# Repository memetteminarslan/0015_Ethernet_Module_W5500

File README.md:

# 0015_Ethernet_Module_W5500
You are seeing a large number of widely used Ethernet modules in electronic development kits. More information coming soon...

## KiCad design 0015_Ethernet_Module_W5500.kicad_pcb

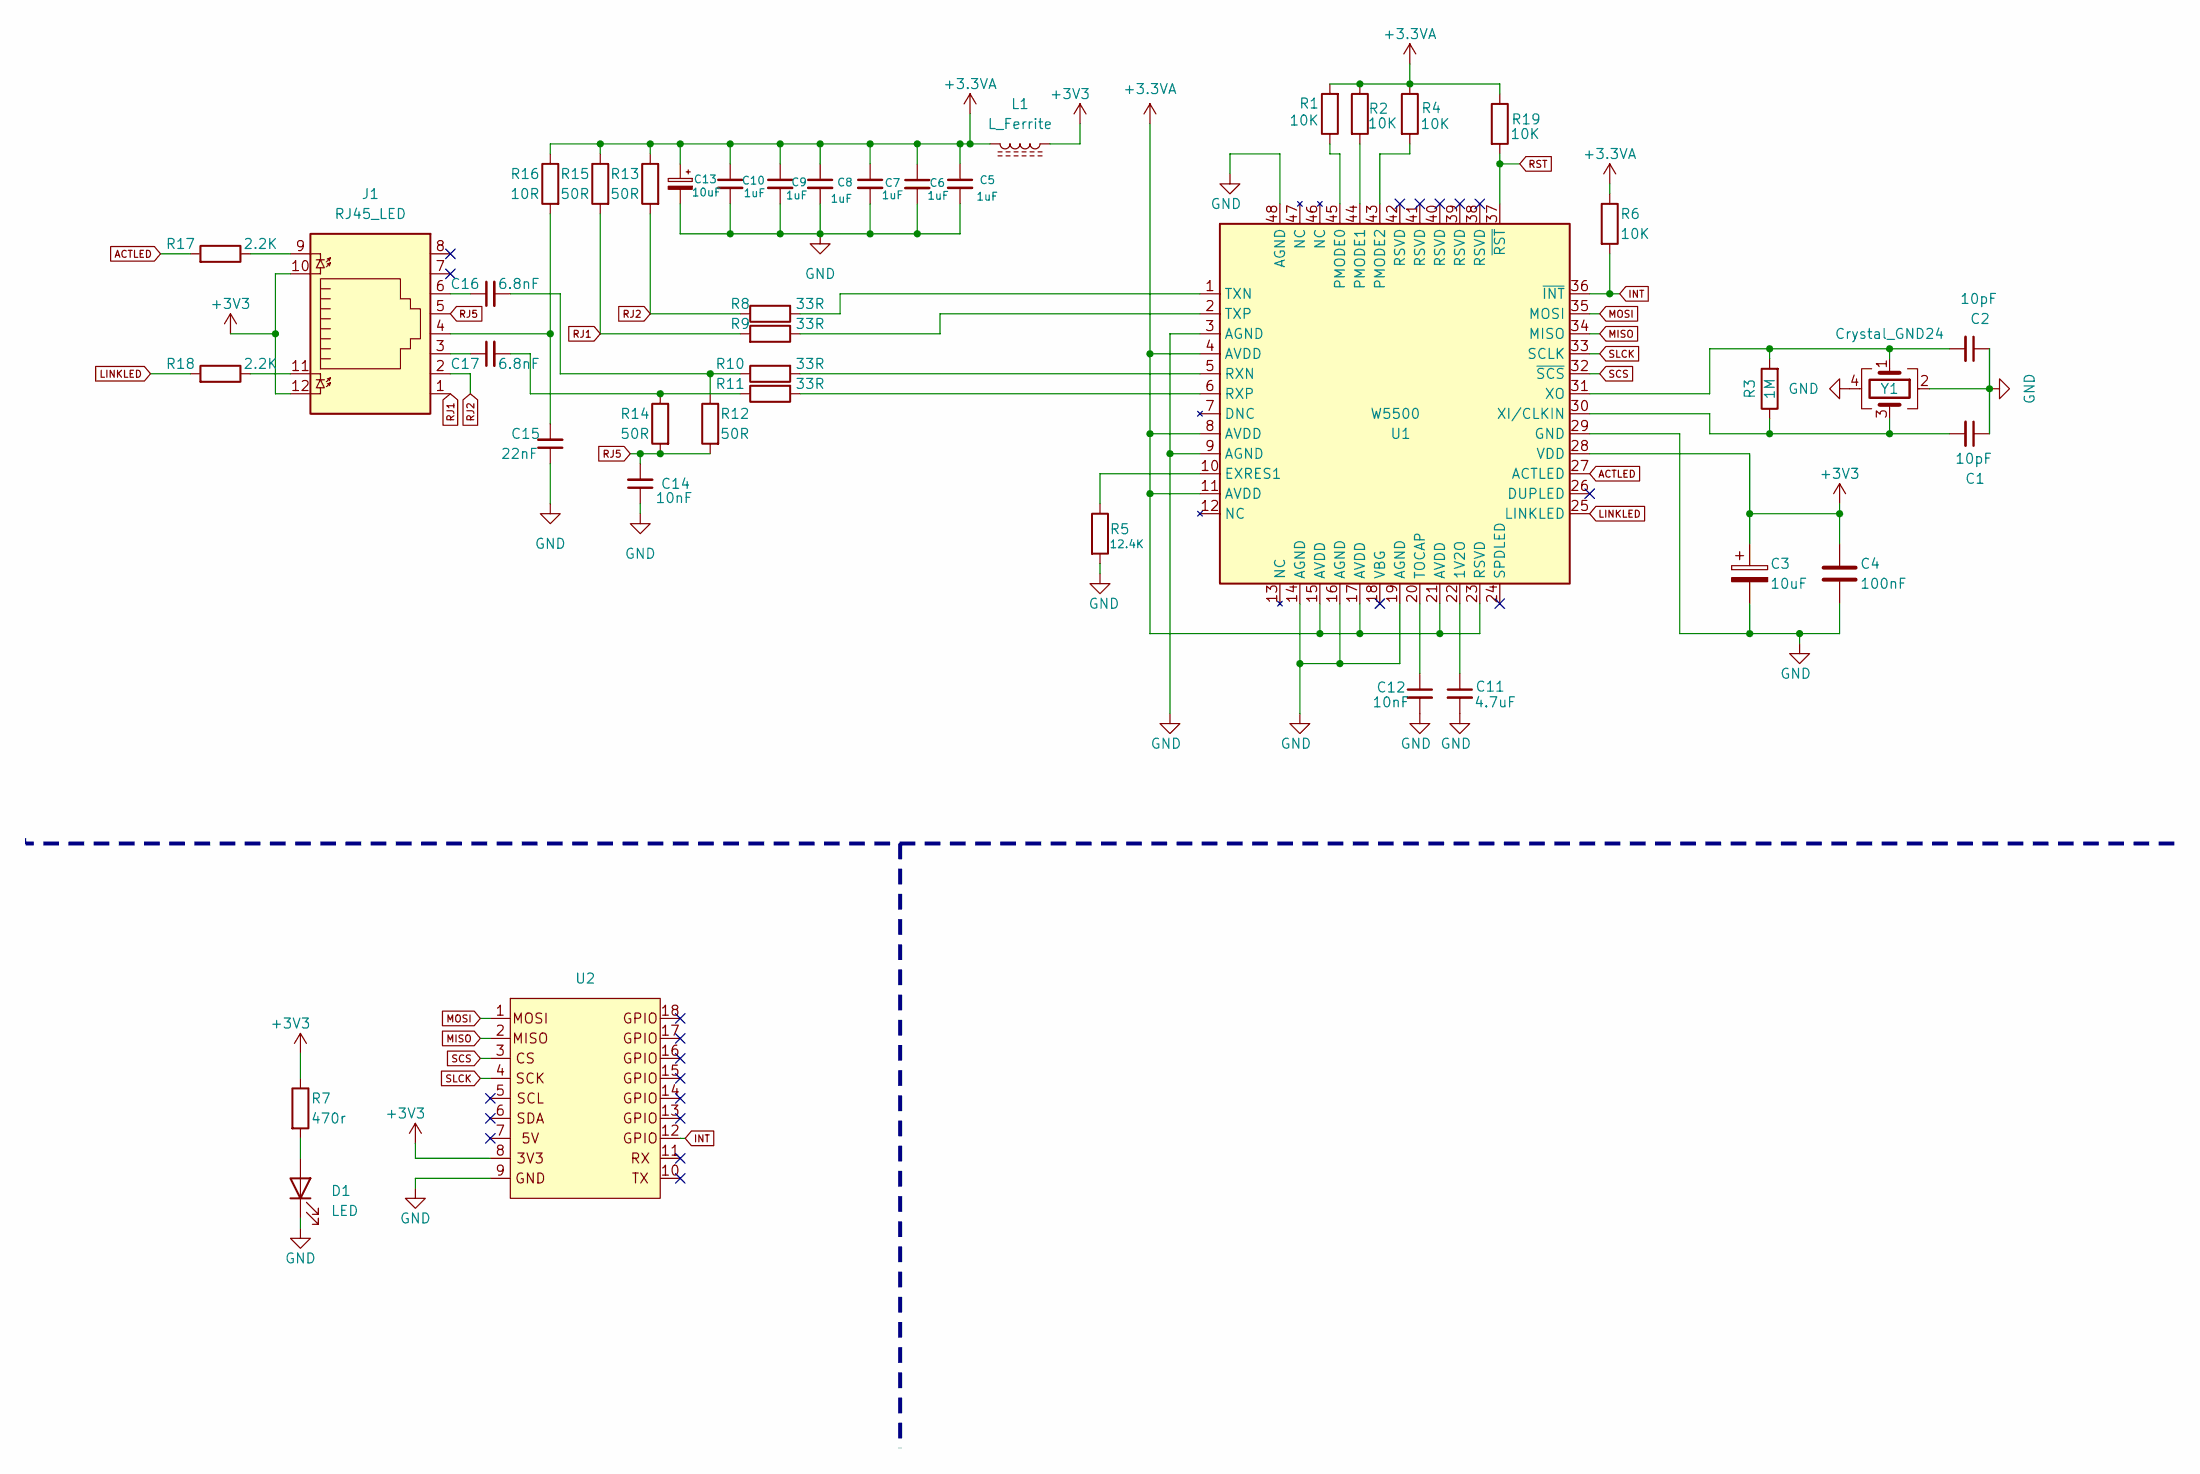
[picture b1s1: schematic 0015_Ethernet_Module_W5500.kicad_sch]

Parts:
C1, C2: 10pF; C_0805_2012Metric
C3, C13: 10uF; CP_EIA-3216-10_Kemet-I
C4: 100nF; C_0805_2012Metric
C5, C6, C7, C8, C9, C10: 1uF; C_0805_2012Metric
C11: 4.7uF; C_0805_2012Metric
C12, C14: 10nF; C_0805_2012Metric
C15: 22nF; C_0805_2012Metric
C16, C17: 6.8nF; C_0805_2012Metric
D1: LED; LED_0805_2012Metric
J1: RJ45_LED; RJ45_Hanrun_HR911105A
L1: L_Ferrite; C_0603_1608Metric
R1, R2, R4, R6, R19: 10K; R_0805_2012Metric
R3: 1M; R_0805_2012Metric
R5: 12.4K; R_0805_2012Metric
R7: 470r; R_0805_2012Metric
R8, R9, R10, R11: 33R; R_0805_2012Metric
R12, R13, R14, R15: 50R; R_0805_2012Metric
R16: 10R; R_0805_2012Metric
R17, R18: 2.2K; R_0805_2012Metric
U1: W5500; LQFP-48_7x7mm_P0.5mm
U2: pin_header_5-3
Y1: Crystal_GND24; Crystal_SMD_EuroQuartz_MT-4Pin_3.2x2.5mm

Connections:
+3.3VA: C5.1, C6.1, C7.1, C8.1, C9.1, C10.1, C13.1, L1.1, R1.2, R2.1, R4.1, R6.1, R13.1, R15.1, R16.1, R19.1, U1.4 (AVDD), U1.8 (AVDD), U1.11 (AVDD), U1.15 (AVDD), U1.17 (AVDD), U1.21 (AVDD), U1.23 (RSVD)
+3V3: C3.1, C4.1, J1.10, J1.12, L1.2, R7.1, U1.28 (VDD), U2.8
ACTLED: R17.2, U1.27 (ACTLED)
GND: C1.1, C2.1, C3.2, C4.2, C5.2, C6.2, C7.2, C8.2, C9.2, C10.2, C11.2, C12.2, C13.2, C14.1, C15.1, D1.1 (K), R5.2, U1.3 (AGND), U1.9 (AGND), U1.14 (AGND), U1.16 (AGND), U1.19 (AGND), U1.29 (GND), U1.48 (AGND), U2.9, Y1.2, Y1.4
INT: R6.2, U1.36 (~INT), U2.12
LINKLED: R18.2, U1.25 (LINKLED)
MISO: U1.34 (MISO), U2.2
MOSI: U1.35 (MOSI), U2.1
unnamed: C15.2, J1.4, R16.2
unnamed: C16.1, J1.6
unnamed: C16.2, R10.1, R12.1
unnamed: C17.1, J1.3
unnamed: C17.2, R11.1, R14.1
unnamed: D1.2 (A), R7.2
unnamed: J1.9, R17.1
unnamed: J1.11, R18.1
unnamed: C11.1, U1.22 (1V2O)
unnamed: R5.1, U1.10 (EXRES1)
unnamed: R1.1, U1.45 (PMODE0)
unnamed: R2.2, U1.44 (PMODE1)
unnamed: R4.2, U1.43 (PMODE2)
unnamed: R10.2, U1.5 (RXN)
unnamed: R11.2, U1.6 (RXP)
unnamed: C12.1, U1.20 (TOCAP)
unnamed: R8.2, U1.1 (TXN)
unnamed: R9.1, U1.2 (TXP)
unnamed: C1.2, R3.1, U1.30 (XI/CLKIN), Y1.3
unnamed: C2.2, R3.2, U1.31 (XO), Y1.1
RJ1: J1.1, R9.2, R15.2
RJ2: J1.2, R8.1, R13.2
RJ5: C14.2, J1.5, R12.2, R14.2
RST: R19.2, U1.37 (~RST)
SCS: U1.32 (~SCS), U2.3
SLCK: U1.33 (SCLK), U2.4

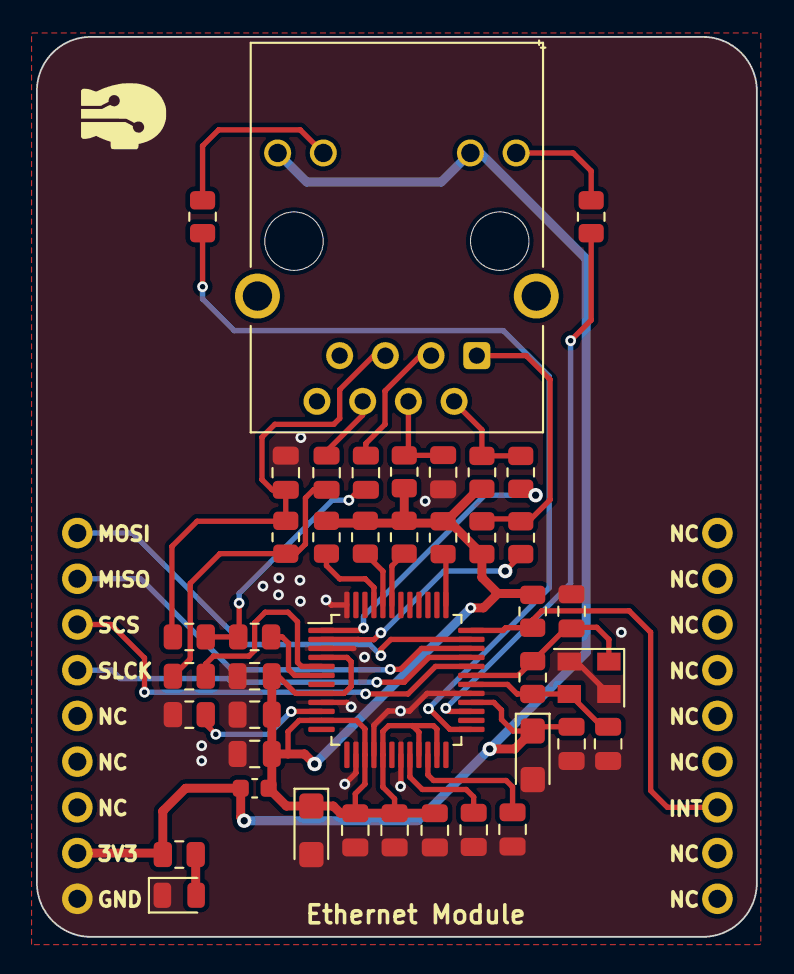
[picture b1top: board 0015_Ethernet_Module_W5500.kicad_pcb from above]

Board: 2 copper layers, 40.0 x 50.0 mm, 42 parts (0 on the bottom side), 34 nets.
